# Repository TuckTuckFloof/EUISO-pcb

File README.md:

# EUISO-pcb
 Oh Lord, what is this trainwreck

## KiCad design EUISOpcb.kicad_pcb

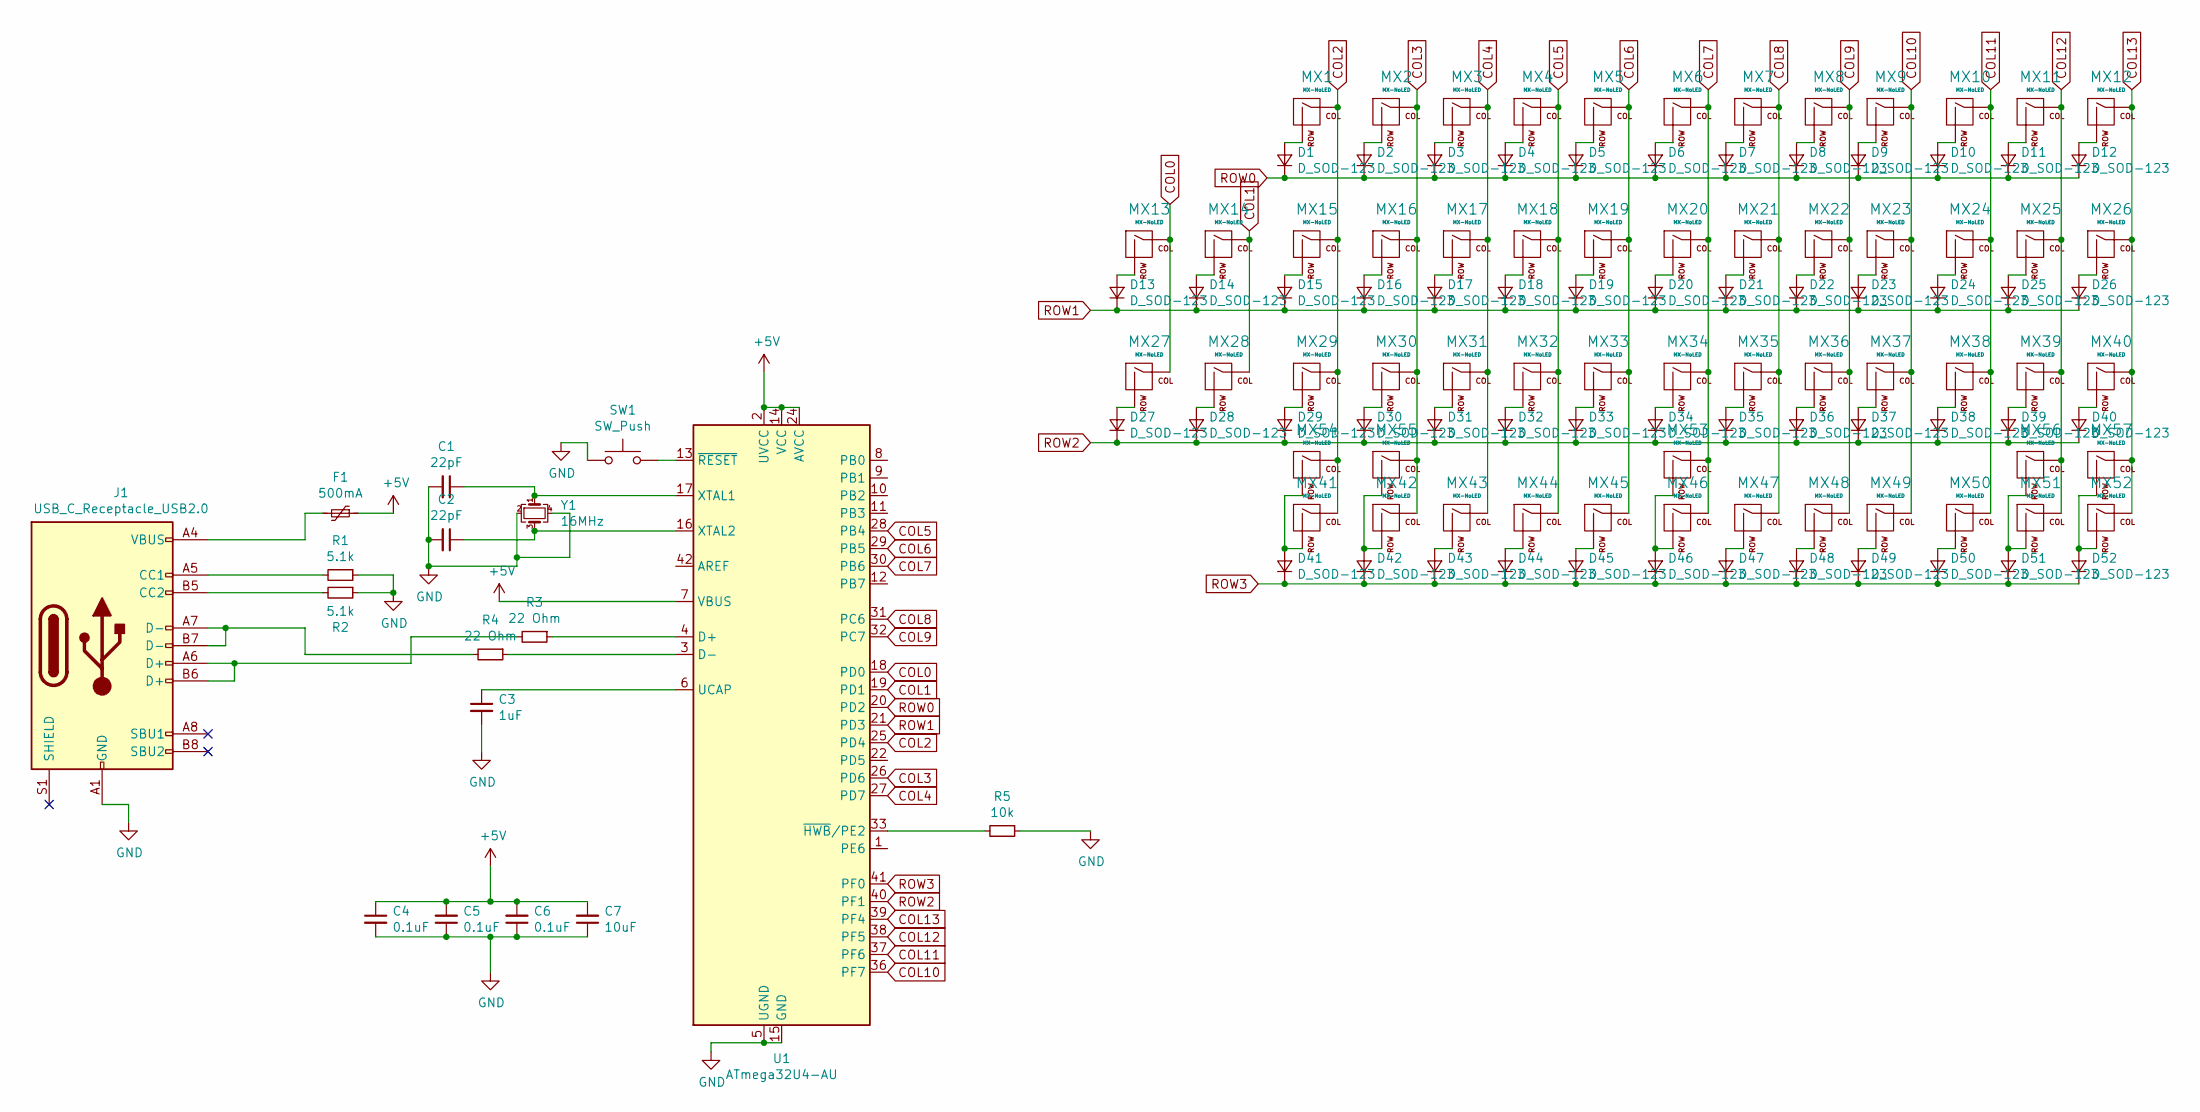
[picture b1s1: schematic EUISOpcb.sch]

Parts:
C1, C2: 22pF; C_0805_2012Metric
C3: 1uF; C_0805_2012Metric
C4, C5, C6: 0.1uF; C_0805_2012Metric
C7: 10uF; C_0805_2012Metric
D1, D2, D3, D4, D5, D6, D7, D8, D9, D10, D11, D12, D13, D14, D15, D16, D17, D18, D19, D20, D21, D22, D23, D24, D25, D26, D27, D28, D29, D30, D31, D32, D33, D34, D35, D36, D37, D38, D39, D40, D41, D42, D43, D44, D45, D46, D47, D48, D49, D50, D51, D52: D_SOD-123
F1: 500mA; Fuse_1206_3216Metric
J1: USB_C_Receptacle_USB2.0; USB_C_Receptacle_HRO_TYPE-C-31-M-12
MX1, MX2, MX3, MX4, MX5, MX6, MX7, MX8, MX9, MX10, MX11, MX12, MX15, MX16, MX17, MX18, MX19, MX20, MX21, MX22, MX23, MX24, MX25, MX26, MX29, MX30, MX31, MX32, MX33, MX34, MX35, MX36, MX37, MX38, MX39, MX40, MX41, MX42, MX43, MX44, MX45, MX46, MX47, MX48, MX49, MX50, MX51, MX52: MX-NoLED; MXOnly-1U-NoLED
MX13, MX14, MX27, MX28: MX-NoLED; MXOnly-ISO
MX53: MX-NoLED; MXOnly-7U-ReversedStabilizers-NoLED
MX54, MX55, MX56, MX57: MX-NoLED; MXOnly-1.25U-NoLED
R1, R2: 5.1k; R_0805_2012Metric
R3, R4: 22 Ohm; R_0805_2012Metric
R5: 10k; R_0805_2012Metric
SW1: SW_Push; SKQG-1155865
U1: ATmega32U4-AU; TQFP-44_10x10mm_P0.8mm; LCSC C44854
Y1: 16MHz; Crystal_SMD_3225-4Pin_3.2x2.5mm

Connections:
+5V: C4.1, C5.2, C6.2, C7.2, F1.1, U1.2 (UVCC), U1.7 (VBUS), U1.14 (VCC), U1.24 (AVCC), U1.34 (VCC), U1.44 (AVCC)
COL0: MX13.1 (COL), MX27.1 (COL), U1.18 (PD0)
COL1: MX14.1 (COL), MX28.1 (COL), U1.19 (PD1)
COL2: MX1.1 (COL), MX15.1 (COL), MX29.1 (COL), MX41.1 (COL), MX54.1 (COL), U1.25 (PD4)
COL3: MX2.1 (COL), MX16.1 (COL), MX30.1 (COL), MX42.1 (COL), MX55.1 (COL), U1.26 (PD6)
COL4: MX3.1 (COL), MX17.1 (COL), MX31.1 (COL), MX43.1 (COL), U1.27 (PD7)
COL5: MX4.1 (COL), MX18.1 (COL), MX32.1 (COL), MX44.1 (COL), U1.28 (PB4)
COL6: MX5.1 (COL), MX19.1 (COL), MX33.1 (COL), MX45.1 (COL), U1.29 (PB5)
COL7: MX6.1 (COL), MX20.1 (COL), MX34.1 (COL), MX46.1 (COL), MX53.1 (COL), U1.30 (PB6)
COL8: MX7.1 (COL), MX21.1 (COL), MX35.1 (COL), MX47.1 (COL), U1.31 (PC6)
COL9: MX8.1 (COL), MX22.1 (COL), MX36.1 (COL), MX48.1 (COL), U1.32 (PC7)
COL10: MX9.1 (COL), MX23.1 (COL), MX37.1 (COL), MX49.1 (COL), U1.36 (PF7)
COL11: MX10.1 (COL), MX24.1 (COL), MX38.1 (COL), MX50.1 (COL), U1.37 (PF6)
COL12: MX11.1 (COL), MX25.1 (COL), MX39.1 (COL), MX51.1 (COL), MX56.1 (COL), U1.38 (PF5)
COL13: MX12.1 (COL), MX26.1 (COL), MX40.1 (COL), MX52.1 (COL), MX57.1 (COL), U1.39 (PF4)
GND: C1.2, C2.2, C3.2, C4.2, C5.1, C6.1, C7.1, J1.A1 (GND), J1.A12 (GND), J1.B1 (GND), J1.B12 (GND), R1.1, R2.1, R5.1, SW1.1, U1.5 (UGND), U1.15 (GND), U1.23 (GND), U1.35 (GND), U1.43 (GND), Y1.2, Y1.4
unnamed: C1.1, U1.17 (XTAL1), Y1.1
unnamed: C2.1, U1.16 (XTAL2), Y1.3
unnamed: C3.1, U1.6 (UCAP)
unnamed: D1.2 (A), MX1.2 (ROW)
unnamed: D2.2 (A), MX2.2 (ROW)
unnamed: D3.2 (A), MX3.2 (ROW)
unnamed: D4.2 (A), MX4.2 (ROW)
unnamed: D5.2 (A), MX5.2 (ROW)
unnamed: D6.2 (A), MX6.2 (ROW)
unnamed: D7.2 (A), MX7.2 (ROW)
unnamed: D8.2 (A), MX8.2 (ROW)
unnamed: D9.2 (A), MX9.2 (ROW)
unnamed: D10.2 (A), MX10.2 (ROW)
unnamed: D11.2 (A), MX11.2 (ROW)
unnamed: D12.2 (A), MX12.2 (ROW)
unnamed: D13.2 (A), MX13.2 (ROW)
unnamed: D14.2 (A), MX14.2 (ROW)
unnamed: D15.2 (A), MX15.2 (ROW)
unnamed: D16.2 (A), MX16.2 (ROW)
unnamed: D17.2 (A), MX17.2 (ROW)
unnamed: D18.2 (A), MX18.2 (ROW)
unnamed: D19.2 (A), MX19.2 (ROW)
unnamed: D20.2 (A), MX20.2 (ROW)
unnamed: D21.2 (A), MX21.2 (ROW)
unnamed: D22.2 (A), MX22.2 (ROW)
unnamed: D23.2 (A), MX23.2 (ROW)
unnamed: D24.2 (A), MX24.2 (ROW)
unnamed: D25.2 (A), MX25.2 (ROW)
unnamed: D26.2 (A), MX26.2 (ROW)
unnamed: D27.2 (A), MX27.2 (ROW)
unnamed: D28.2 (A), MX28.2 (ROW)
unnamed: D29.2 (A), MX29.2 (ROW)
unnamed: D30.2 (A), MX30.2 (ROW)
unnamed: D31.2 (A), MX31.2 (ROW)
unnamed: D32.2 (A), MX32.2 (ROW)
unnamed: D33.2 (A), MX33.2 (ROW)
unnamed: D34.2 (A), MX34.2 (ROW)
unnamed: D35.2 (A), MX35.2 (ROW)
unnamed: D36.2 (A), MX36.2 (ROW)
unnamed: D37.2 (A), MX37.2 (ROW)
unnamed: D38.2 (A), MX38.2 (ROW)
unnamed: D39.2 (A), MX39.2 (ROW)
unnamed: D40.2 (A), MX40.2 (ROW)
unnamed: D41.2 (A), MX41.2 (ROW), MX54.2 (ROW)
unnamed: D42.2 (A), MX42.2 (ROW), MX55.2 (ROW)
unnamed: D43.2 (A), MX43.2 (ROW)
unnamed: D44.2 (A), MX44.2 (ROW)
unnamed: D45.2 (A), MX45.2 (ROW)
unnamed: D46.2 (A), MX46.2 (ROW), MX53.2 (ROW)
unnamed: D47.2 (A), MX47.2 (ROW)
unnamed: D48.2 (A), MX48.2 (ROW)
unnamed: D49.2 (A), MX49.2 (ROW)
unnamed: D50.2 (A), MX50.2 (ROW)
unnamed: D51.2 (A), MX51.2 (ROW), MX56.2 (ROW)
unnamed: D52.2 (A), MX52.2 (ROW), MX57.2 (ROW)
unnamed: F1.2, J1.A4 (VBUS), J1.A9 (VBUS), J1.B4 (VBUS), J1.B9 (VBUS)
unnamed: J1.A5 (CC1), R1.2
unnamed: J1.A6 (D+), J1.B6 (D+), R3.2
unnamed: J1.A7 (D-), J1.B7 (D-), R4.2
unnamed: J1.B5 (CC2), R2.2
unnamed: R3.1, U1.4 (D+)
unnamed: R4.1, U1.3 (D-)
unnamed: R5.2, U1.33 (~HWB~/PE2)
unnamed: SW1.2, U1.13 (~RESET)
ROW0: D1.1 (K), D2.1 (K), D3.1 (K), D4.1 (K), D5.1 (K), D6.1 (K), D7.1 (K), D8.1 (K), D9.1 (K), D10.1 (K), D11.1 (K), D12.1 (K), U1.20 (PD2)
ROW1: D13.1 (K), D14.1 (K), D15.1 (K), D16.1 (K), D17.1 (K), D18.1 (K), D19.1 (K), D20.1 (K), D21.1 (K), D22.1 (K), D23.1 (K), D24.1 (K), D25.1 (K), D26.1 (K), U1.21 (PD3)
ROW2: D27.1 (K), D28.1 (K), D29.1 (K), D30.1 (K), D31.1 (K), D32.1 (K), D33.1 (K), D34.1 (K), D35.1 (K), D36.1 (K), D37.1 (K), D38.1 (K), D39.1 (K), D40.1 (K), U1.40 (PF1)
ROW3: D41.1 (K), D42.1 (K), D43.1 (K), D44.1 (K), D45.1 (K), D46.1 (K), D47.1 (K), D48.1 (K), D49.1 (K), D50.1 (K), D51.1 (K), D52.1 (K), U1.41 (PF0)

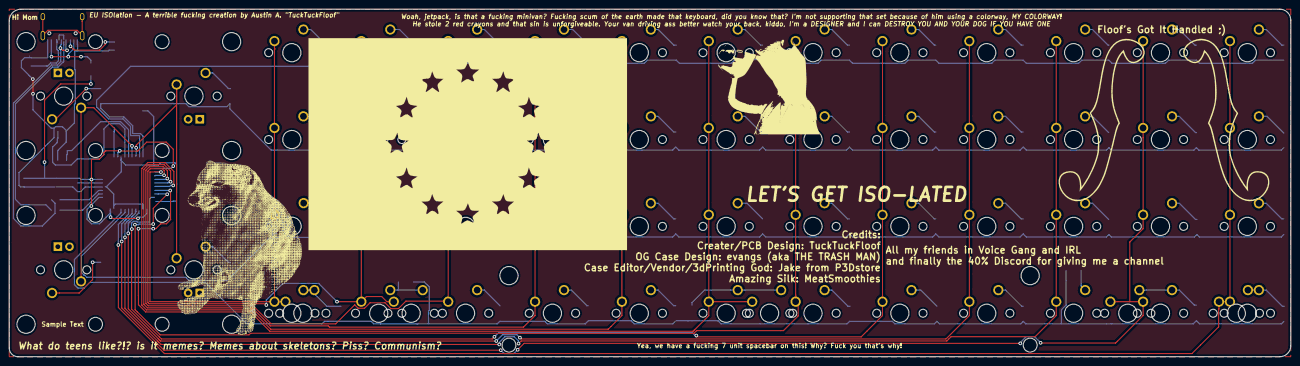
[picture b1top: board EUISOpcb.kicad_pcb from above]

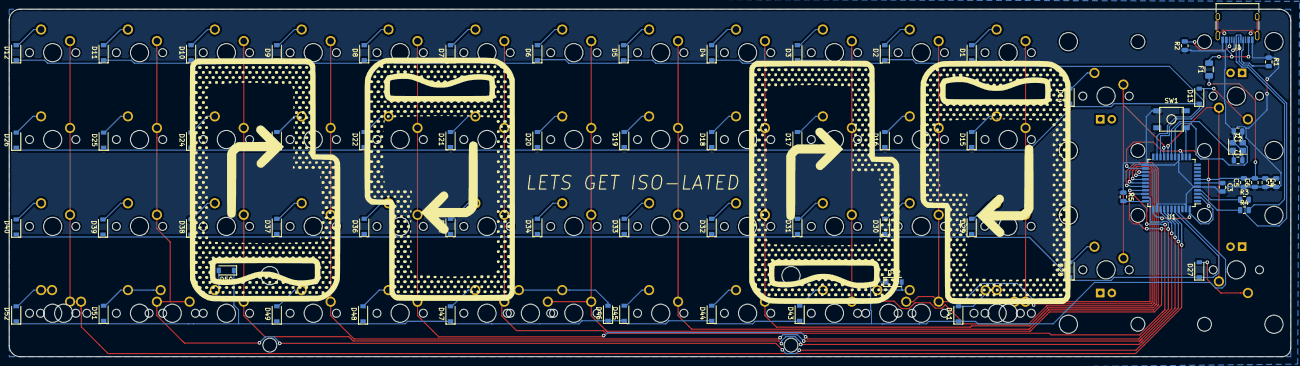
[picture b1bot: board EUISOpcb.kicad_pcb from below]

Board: 2 copper layers, 281.1 x 76.2 mm, 125 parts (69 on the bottom side), 83 nets.

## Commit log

2019-10-12 Adding the necessities
2019-10-13 Adding the submodules to make my life easier
2019-10-16 Adding Keymaps
2019-12-23 I got the Atmega
2020-01-25 PCB Schematic/Traces Complete
    Completed the PCB Schematic and traces!
2020-01-29 Completed PCB
    Completed the PCB by adding 7u Support and new decorations
2020-02-04 Cheems
    Cheems
2020-04-29 Idk what I did this time
    But it was definitely something, it is complete though
2020-09-21 Complete
    finished with gerbers
2020-09-21 ok now it's finished
    I added the plate and BOM files to the gerbers
2021-06-16 updating files for comp transfer
